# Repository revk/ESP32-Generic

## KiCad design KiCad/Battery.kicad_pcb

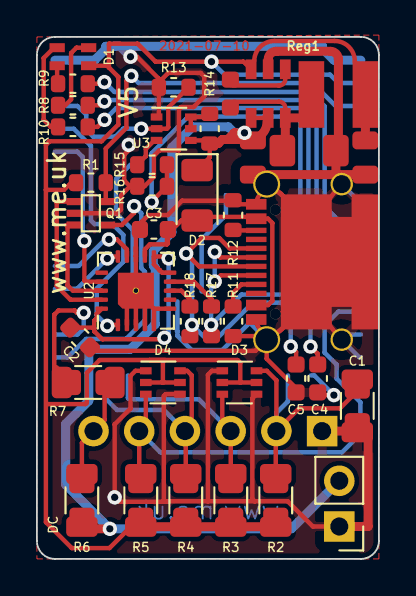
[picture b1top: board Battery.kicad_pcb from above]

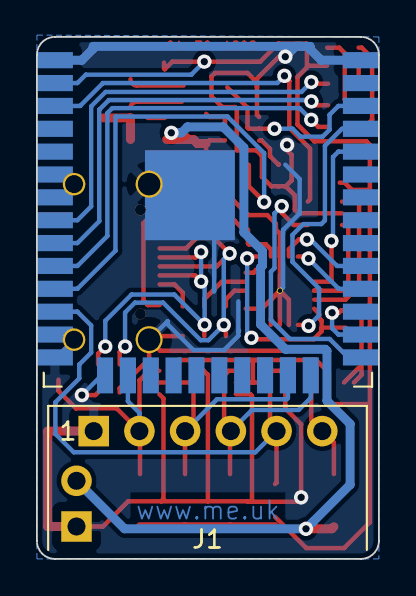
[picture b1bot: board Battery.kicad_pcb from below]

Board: 2 copper layers, 19.0 x 29.0 mm, 35 parts (2 on the bottom side), 35 nets.

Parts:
C1: NF; Pad_1206_0805_NF
C2: 100nF; C_0603
C3: 10nF; C_0603
C4, C5: 47pF; C_0603
D1: RGB; LED-RGB-1.6x1.6
D2: D; D_1206_3216Metric
D3, D4: BAV99S; SOT-363_SC-70-6
J1: Connector; Molex_MiniSPOX_H6RA_0.1
J2: USB-C; USC16-TR-Round
J3: DC; PinHeader_1x02_P2.54mm_Vertical
Q1: RN1701; USV-5
R1, R13, R14: 10K; R_0603
R2, R3, R4, R5, R6: NF; Pad_1206_0805_NF
R7: 0R; Pad_1206_0805_NF
R8: 324R; R_0603
R9: 732R; R_0603
R10: 1K; R_0603
R11, R12: 5K1; R_0603
R15: 18K; R_0603
R16: 1k; R_0603
R17, R18: 27R; R_0603
Reg1: Regulator; RegulatorBlock
U1: ESP32-WROOM-32
U2: FT231XQ; QFN-20-1EP_4x4mm_P0.5mm_EP2.5x2.5mm
U3: NX6020CAKS; SOT-363_SC-70-6

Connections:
+3V3: D1.1, D3.2, D3.5, D4.2, D4.5, R1.2, R2.1, R3.1, R4.1, R5.1, Reg1.4, U1.2
ADC: R15.2, R16.1, U1.11
ADCON: R13.2, U1.36, U3.2
B: R8.2, U1.9
CHARGER: U1.29, U2.14
D+: R18.1, U2.8
D-: R17.2, U2.9
DC: D2.1, J3.2, R6.1, R14.2, Reg1.1, Reg1.2, U3.4
EN: Q1.1, U2.19
G: R10.2, U1.10
GND: C1.1, C2.2, C3.1, C4.2, C5.2, D3.1, D3.4, D4.1, D4.4, J1.1, J2.A1, J2.A12, J2.B1, J2.B12, J2.S1, J3.1, Q1.2, R11.2, R12.1, R13.1, R16.2, Reg1.3, U1.1, U1.6, U1.7, U1.13, U1.14, U1.15, U1.38, U1.39, U2.2, U2.3, U2.4, U2.5, U2.6, U2.13, U2.21, U3.1
GPIO0: Q1.3, U2.18
I: U1.34, U2.17
IO1: C1.2, D3.6, J1.2, R2.2, U1.16
IO2: D3.3, J1.3, R3.2, U1.23
IO3: D4.6, J1.4, R4.2, U1.24
IO4: D4.3, J1.5, R5.2, U1.12
IO5: R7.1, U1.26
unnamed: C2.1, U2.10, U2.11, U2.20
unnamed: C4.1, J2.A7, J2.B7, R17.1
unnamed: C5.1, J2.A6, J2.B6, R18.2
unnamed: D1.2, R9.1
unnamed: D1.3, R10.1
unnamed: D1.4, R8.1
unnamed: J1.6, R6.2, R7.2
unnamed: J2.A5, R11.1
unnamed: J2.B5, R12.2
unnamed: Q1.4, U1.25
unnamed: Q1.5, R1.1, U1.3
unnamed: R14.1, U3.5, U3.6
unnamed: R15.1, U3.3
O: U1.35, U2.1
R: R9.2, U1.8
USB: U1.28, U2.15
VBUS: C3.2, D2.2, J2.A4, J2.A9, J2.B4, J2.B9, U2.12

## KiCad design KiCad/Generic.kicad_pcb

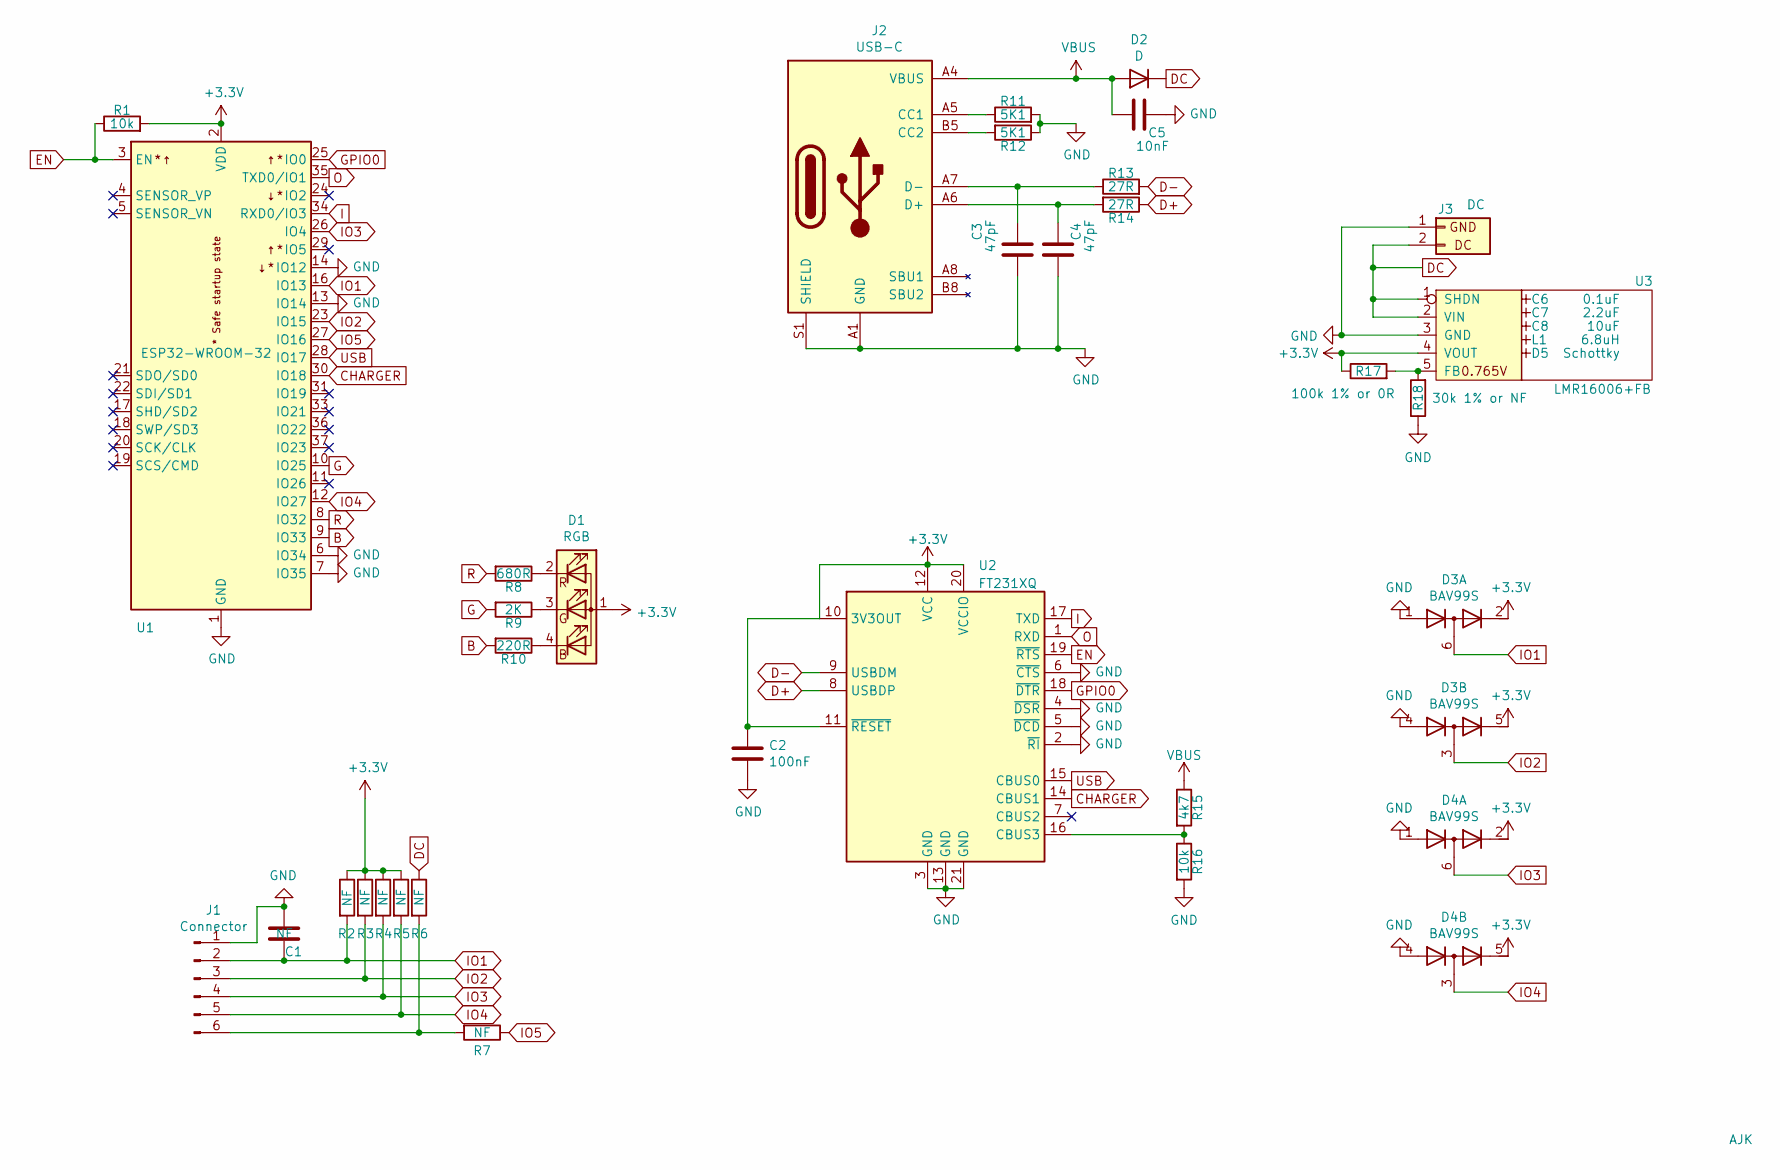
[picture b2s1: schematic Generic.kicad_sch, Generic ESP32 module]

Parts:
C1: NF; Pad_1206_0805_Open
C2: 100nF; C_0603
C3, C4: 47pF; C_0603
C5: 10nF; C_0603
C6: 0.1uF; Hidden
C7: 2.2uF; Hidden
C8: 10uF; Hidden
D1: RGB; LED-RGB-1.6x1.6; Part No APTF1616LSEEZGKQBKC
D2: D; D_1206_3216Metric
D3, D4: BAV99S; SOT-363_SC-70-6; Part No BAV99S
D5: Schottky; Hidden; Part No CD1206-B2100
J1: Connector; Molex_MiniSPOX_H6RA; Part No 0022057065
J2: USB-C; USC16-TR-Round; Part No CSP-USC16-TR
J3: DC
L1: 6.8uH; Hidden; Part No TYA4020
Logo1: AJK
R1, R16: 10k; R_0603
R2, R3, R4, R5, R6, R7: NF; Pad_1206_0805_Open
R8: 680R; R_0603
R9: 2K; R_0603
R10: 220R; R_0603
R11, R12: 5K1; R_0603
R13, R14: 27R; R_0603
R15: 4k7; R_0603
R17: 100k 1% or 0R; R_0603
R18: 30k 1% or NF; R_0603
U1: ESP32-WROOM-32
U2: FT231XQ; QFN-20-1EP_4x4mm_P0.5mm_EP2.5x2.5mm
U3: LMR16006+FB; RegulatorBlockFB; Part No LMR16006YQ3

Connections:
+3V3: C2.1, D1.1 (A), D3.2 (K2), D3.5 (K4), D4.2 (K2), D4.5 (K4), R1.2, R2.1, R3.1, R4.1, R5.1, R17.1, U1.2 (VDD), U2.10 (3V3OUT), U2.11 (~RESET), U2.12 (VCC), U2.20 (VCCIO), U3.4 (VOUT)
B: R10.2, U1.9 (IO33)
CHARGER: U1.30 (IO18), U2.14 (CBUS1)
D+: R14.1, U2.8 (USBDP)
D-: R13.2, U2.9 (USBDM)
DC: D2.1 (K), J3.2 (DC), R6.1, U3.1 (SHDN), U3.2 (VIN)
EN: R1.1, U1.3 (EN), U2.19 (~RTS)
G: R9.2, U1.10 (IO25)
GND: C1.1, C2.2, C3.2, C4.2, C5.1, D3.1 (A1), D3.4 (A3), D4.1 (A1), D4.4 (A3), J1.1, J2.A1 (GND), J2.A12 (GND), J2.B1 (GND), J2.B12 (GND), J2.S1 (SHIELD), J3.1 (GND), R11.2, R12.1, R16.2, R18.1, U1.1 (GND), U1.6 (IO34), U1.7 (IO35), U1.13 (IO14), U1.14 (IO12), U1.15 (GND), U1.38 (GND), U1.39 (GND), U2.2 (~RI), U2.3 (GND), U2.4 (~DSR), U2.5 (~DCD), U2.6 (~CTS), U2.13 (GND), U2.21 (GND), U3.3 (GND)
GPIO0: U1.25 (IO0), U2.18 (~DTR)
I: U1.34 (RXD0/IO3), U2.17 (TXD)
IO1: C1.2, D3.6 (K3A4), J1.2, R2.2, U1.16 (IO13)
IO2: D3.3 (K1A2), J1.3, R3.2, U1.23 (IO15)
IO3: D4.6 (K3A4), J1.4, R4.2, U1.26 (IO4)
IO4: D4.3 (K1A2), J1.5, R5.2, U1.12 (IO27)
IO5: R7.1, U1.27 (IO16)
unnamed: C3.1, J2.A7 (D-), J2.B7 (D-), R13.1
unnamed: C4.1, J2.A6 (D+), J2.B6 (D+), R14.2
unnamed: D1.2 (RK), R8.1
unnamed: D1.3 (GK), R9.1
unnamed: D1.4 (BK), R10.1
unnamed: J1.6, R6.2, R7.2
unnamed: J2.A5 (CC1), R11.1
unnamed: J2.B5 (CC2), R12.2
unnamed: R15.2, R16.1, U2.16 (CBUS3)
unnamed: R17.2, R18.2, U3.5 (FB)
O: U1.35 (TXD0/IO1), U2.1 (RXD)
R: R8.2, U1.8 (IO32)
USB: U1.28 (IO17), U2.15 (CBUS0)
VBUS: C5.2, D2.2 (A), J2.A4 (VBUS), J2.A9 (VBUS), J2.B4 (VBUS), J2.B9 (VBUS), R15.1

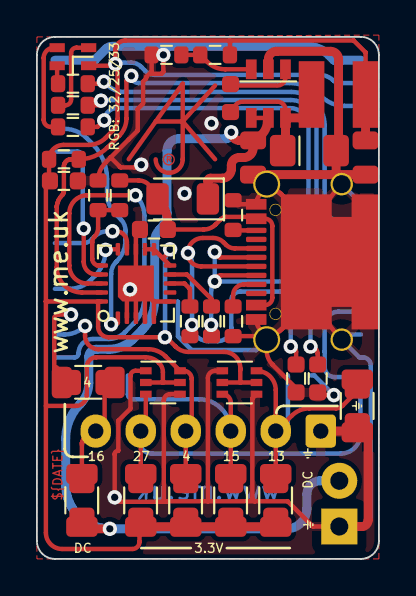
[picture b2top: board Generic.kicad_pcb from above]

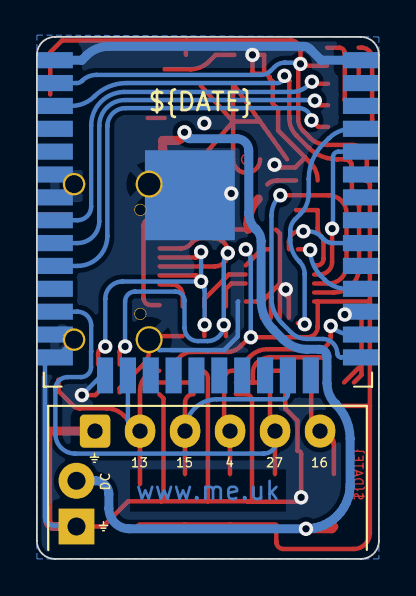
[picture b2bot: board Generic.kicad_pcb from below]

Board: 2 copper layers, 19.0 x 29.0 mm, 39 parts (2 on the bottom side), 30 nets.

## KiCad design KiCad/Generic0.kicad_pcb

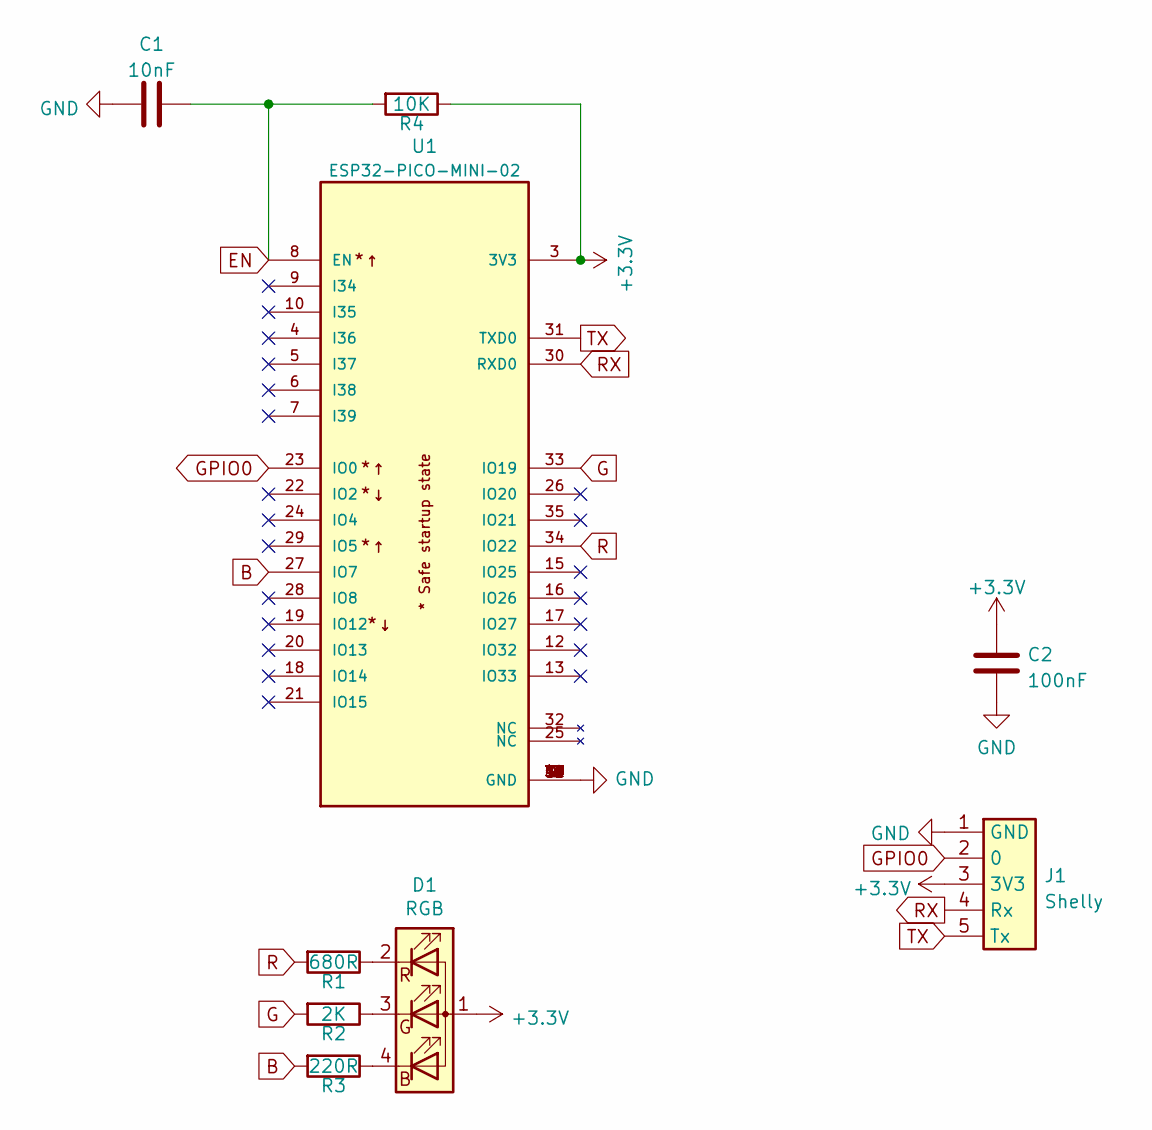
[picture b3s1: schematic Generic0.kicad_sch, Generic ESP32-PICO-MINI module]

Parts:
C1: 10nF; C_0603
C2: 100nF; C_0603
D1: RGB; LED-RGB-1.6x1.6; Part No APTF1616LSEEZGKQBKC
J1: Shelly
R1: 680R; R_0603
R2: 2K; R_0603
R3: 220R; R_0603
R4: 10K; Pad_0603_Bridged
U1: ESP32-PICO-MINI-02; PARTREV v1.0

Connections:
+3V3: C2.1, D1.1 (A), J1.3 (3V3), R4.1, U1.3 (3V3)
B: R3.2, U1.27 (IO7)
EN: C1.2, R4.2, U1.8 (EN)
G: R2.2, U1.33 (IO19)
GND: C1.1, C2.2, J1.1 (GND), U1.1 (GND), U1.2 (GND), U1.11 (GND), U1.14 (GND), U1.36 (GND), U1.37 (GND), U1.38 (GND), U1.39 (GND), U1.40 (GND), U1.41 (GND), U1.42 (GND), U1.43 (GND), U1.44 (GND), U1.45 (GND), U1.46 (GND), U1.47 (GND), U1.48 (GND), U1.49 (GND), U1.50 (GND), U1.51 (GND), U1.52 (GND), U1.53 (GND)
GPIO0: J1.2 (0), U1.23 (IO0)
unnamed: D1.2 (RK), R1.1
unnamed: D1.3 (GK), R2.1
unnamed: D1.4 (BK), R3.1
R: R1.2, U1.34 (IO22)
RX: J1.4 (Rx), U1.30 (RXD0)
TX: J1.5 (Tx), U1.31 (TXD0)

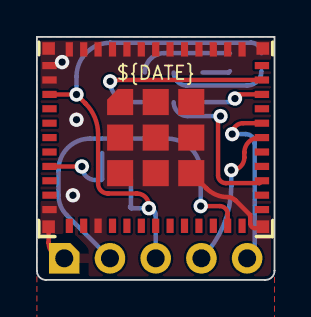
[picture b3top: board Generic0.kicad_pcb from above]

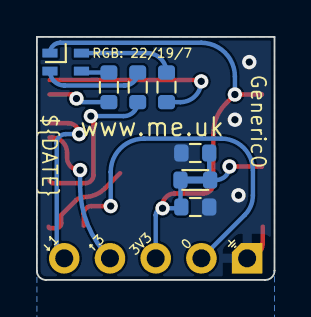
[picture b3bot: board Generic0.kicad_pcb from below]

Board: 2 copper layers, 13.2 x 13.5 mm, 9 parts (8 on the bottom side), 12 nets.

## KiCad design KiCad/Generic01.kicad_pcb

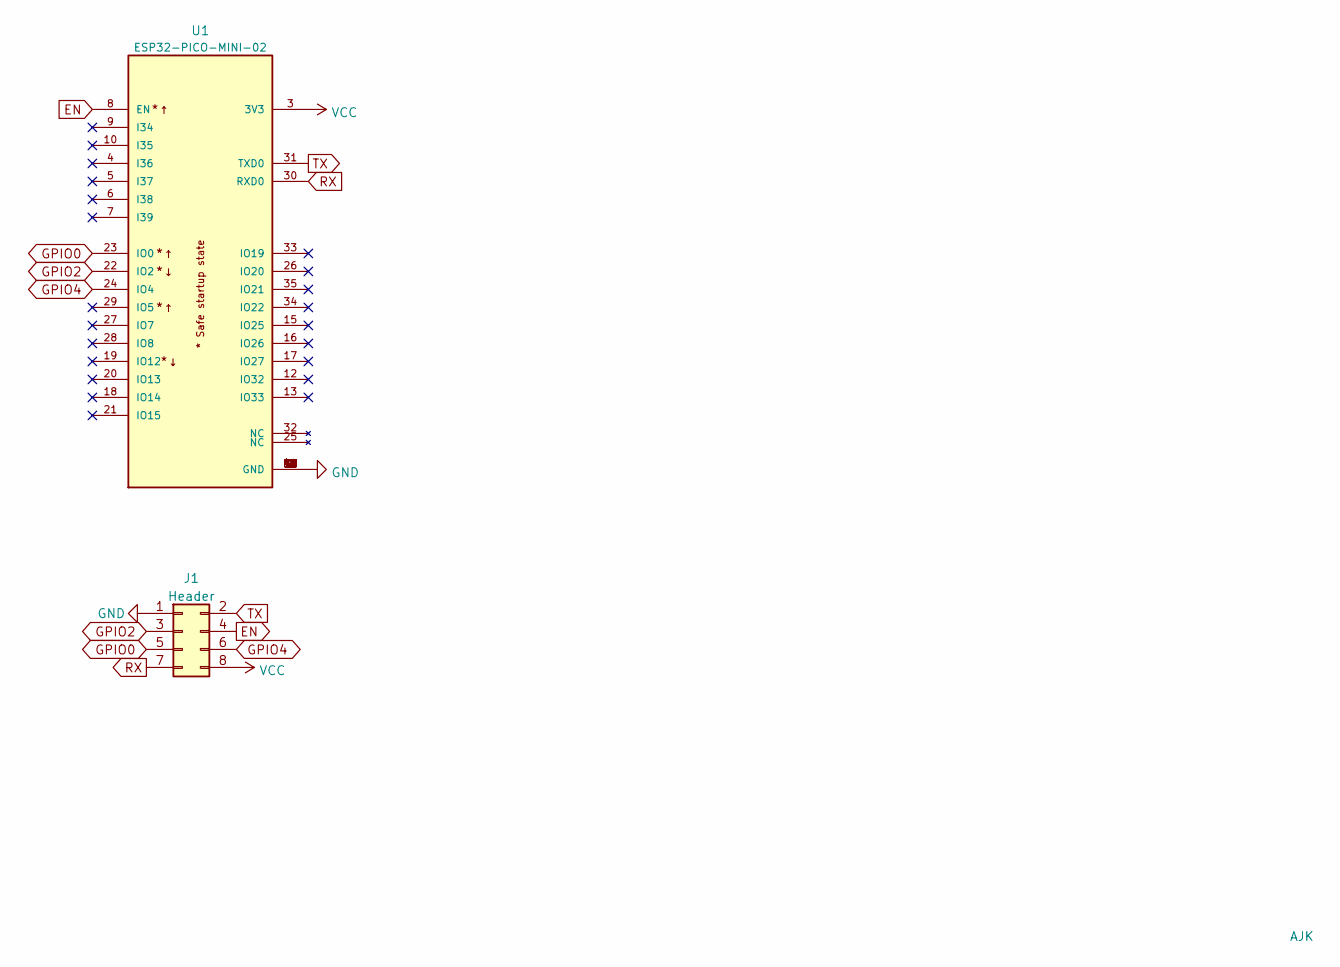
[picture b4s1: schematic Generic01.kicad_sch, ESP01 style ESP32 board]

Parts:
J1: Header; PinHeader_2x04_P2.54mm_Vertical
Logo1: AJK
U1: ESP32-PICO-MINI-02; PARTREV v1.0

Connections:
EN: J1.4, U1.8 (EN)
GND: J1.1, U1.1 (GND), U1.2 (GND), U1.11 (GND), U1.14 (GND), U1.36 (GND), U1.37 (GND), U1.38 (GND), U1.39 (GND), U1.40 (GND), U1.41 (GND), U1.42 (GND), U1.43 (GND), U1.44 (GND), U1.45 (GND), U1.46 (GND), U1.47 (GND), U1.48 (GND), U1.49 (GND), U1.50 (GND), U1.51 (GND), U1.52 (GND), U1.53 (GND)
GPIO0: J1.5, U1.23 (IO0)
GPIO2: J1.3, U1.22 (IO2)
GPIO4: J1.6, U1.24 (IO4)
RX: J1.7, U1.30 (RXD0)
TX: J1.2, U1.31 (TXD0)
VCC: J1.8, U1.3 (3V3)

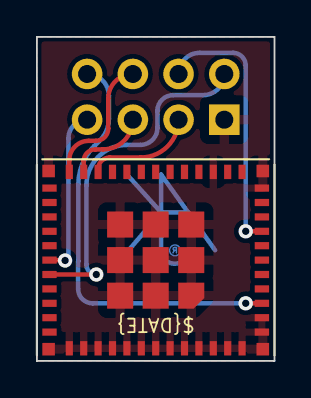
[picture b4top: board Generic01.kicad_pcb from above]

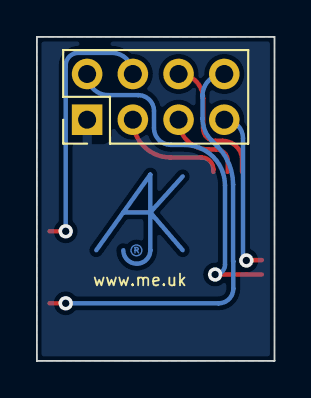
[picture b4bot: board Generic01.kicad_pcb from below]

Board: 2 copper layers, 13.2 x 18.0 mm, 3 parts (2 on the bottom side), 8 nets.

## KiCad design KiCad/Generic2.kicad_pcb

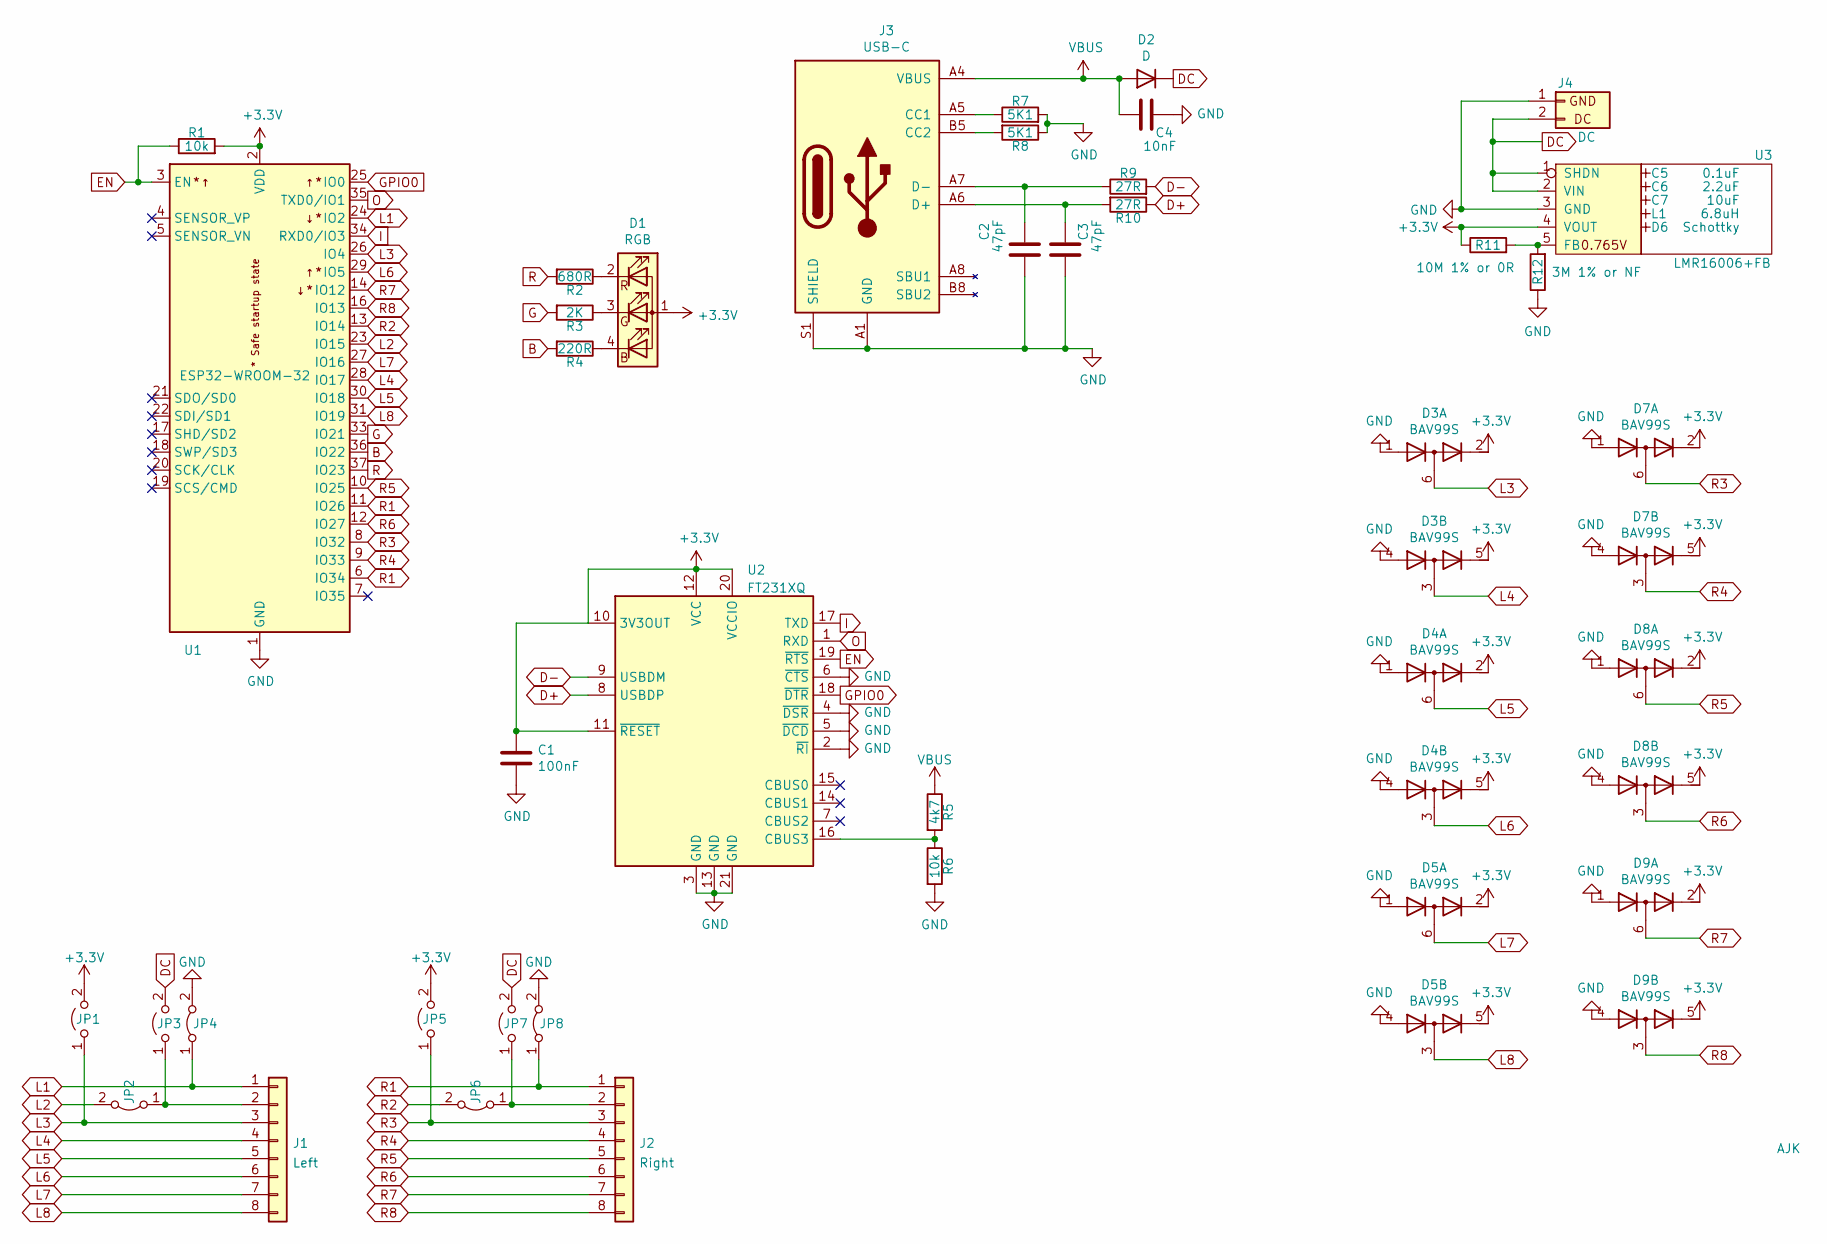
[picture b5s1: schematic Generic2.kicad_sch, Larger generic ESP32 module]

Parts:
C1: 100nF; C_0603
C2, C3: 47pF; C_0603
C4: 10nF; C_0603
C5: 0.1uF; Hidden
C6: 2.2uF; Hidden
C7: 10uF; Hidden
D1: RGB; LED-RGB-1.6x1.6; Part No APTF1616LSEEZGKQBKC
D2: D; D_1206_3216Metric
D3, D4, D5, D7, D8, D9: BAV99S; SOT-363_SC-70-6; Part No BAV99S
D6: Schottky; Hidden; Part No CD1206-B2100
J1: Left; Molex_MiniSPOX_H8RA
J2: Right; Molex_MiniSPOX_H8RA
J3: USB-C; USC16-TR-Round; Part No CSP-USC16-TR
J4: DC; PinHeader_1x02_P2.54mm_Vertical
JP1, JP5: L3; Pad_1206_0805_Open
JP2, JP6: L2; Pad_1206_0805_Bridged
JP3, JP7: L2; Pad_1206_0805_Open
JP4, JP8: L1; Pad_1206_0805_Bridged
L1: 6.8uH; Hidden; Part No TYA4020
Logo1: AJK
R1, R6: 10k; R_0603
R2: 680R; R_0603
R3: 2K; R_0603
R4: 220R; R_0603
R5: 4k7; R_0603
R7, R8: 5K1; R_0603
R9, R10: 27R; R_0603
R11: 10M 1% or 0R; R_0603
R12: 3M 1% or NF; R_0603
U1: ESP32-WROOM-32
U2: FT231XQ; QFN-20-1EP_4x4mm_P0.5mm_EP2.5x2.5mm
U3: LMR16006+FB; RegulatorBlockFB; Part No LMR16006YQ3

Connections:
+3V3: C1.1, D1.1 (A), D3.2 (K2), D3.5 (K4), D4.2 (K2), D4.5 (K4), D5.2 (K2), D5.5 (K4), D7.2 (K2), D7.5 (K4), D8.2 (K2), D8.5 (K4), D9.2 (K2), D9.5 (K4), JP1.2 (B), JP5.2 (B), R1.2, R11.1, U1.2 (VDD), U2.10 (3V3OUT), U2.11 (~RESET), U2.12 (VCC), U2.20 (VCCIO), U3.4 (VOUT)
B: R4.2, U1.36 (IO22)
D+: R10.1, U2.8 (USBDP)
D-: R9.2, U2.9 (USBDM)
DC: D2.1 (K), J4.2 (DC), JP3.2 (B), JP7.2 (B), U3.1 (SHDN), U3.2 (VIN)
EN: R1.1, U1.3 (EN), U2.19 (~RTS)
G: R3.2, U1.33 (IO21)
GND: C1.2, C2.2, C3.2, C4.1, D3.1 (A1), D3.4 (A3), D4.1 (A1), D4.4 (A3), D5.1 (A1), D5.4 (A3), D7.1 (A1), D7.4 (A3), D8.1 (A1), D8.4 (A3), D9.1 (A1), D9.4 (A3), J3.A1 (GND), J3.A12 (GND), J3.B1 (GND), J3.B12 (GND), J3.S1 (SHIELD), J4.1 (GND), JP4.2 (B), JP8.2 (B), R6.2, R7.2, R8.1, R12.1, U1.1 (GND), U1.15 (GND), U1.38 (GND), U1.39 (GND), U2.2 (~RI), U2.3 (GND), U2.4 (~DSR), U2.5 (~DCD), U2.6 (~CTS), U2.13 (GND), U2.21 (GND), U3.3 (GND)
GPIO0: U1.25 (IO0), U2.18 (~DTR)
I: U1.34 (RXD0/IO3), U2.17 (TXD)
L1: J1.1, JP4.1 (A), U1.24 (IO2)
L2: JP2.2 (B), U1.23 (IO15)
L3: D3.6 (K3A4), J1.3, JP1.1 (A), U1.26 (IO4)
L4: D3.3 (K1A2), J1.4, U1.28 (IO17)
L5: D4.6 (K3A4), J1.5, U1.30 (IO18)
L6: D4.3 (K1A2), J1.6, U1.29 (IO5)
L7: D5.6 (K3A4), J1.7, U1.27 (IO16)
L8: D5.3 (K1A2), J1.8, U1.31 (IO19)
unnamed: C2.1, J3.A7 (D-), J3.B7 (D-), R9.1
unnamed: C3.1, J3.A6 (D+), J3.B6 (D+), R10.2
unnamed: D1.2 (RK), R2.1
unnamed: D1.3 (GK), R3.1
unnamed: D1.4 (BK), R4.1
unnamed: J1.2, JP2.1 (A), JP3.1 (A)
unnamed: J2.2, JP6.1 (A), JP7.1 (A)
unnamed: J3.A5 (CC1), R7.1
unnamed: J3.B5 (CC2), R8.2
unnamed: R5.2, R6.1, U2.16 (CBUS3)
unnamed: R11.2, R12.2, U3.5 (FB)
O: U1.35 (TXD0/IO1), U2.1 (RXD)
R: R2.2, U1.37 (IO23)
R1: J2.1, JP8.1 (A), U1.6 (IO34), U1.11 (IO26)
R2: JP6.2 (B), U1.13 (IO14)
R3: D7.6 (K3A4), J2.3, JP5.1 (A), U1.8 (IO32)
R4: D7.3 (K1A2), J2.4, U1.9 (IO33)
R5: D8.6 (K3A4), J2.5, U1.10 (IO25)
R6: D8.3 (K1A2), J2.6, U1.12 (IO27)
R7: D9.6 (K3A4), J2.7, U1.14 (IO12)
R8: D9.3 (K1A2), J2.8, U1.16 (IO13)
VBUS: C4.2, D2.2 (A), J3.A4 (VBUS), J3.A9 (VBUS), J3.B4 (VBUS), J3.B9 (VBUS), R5.1

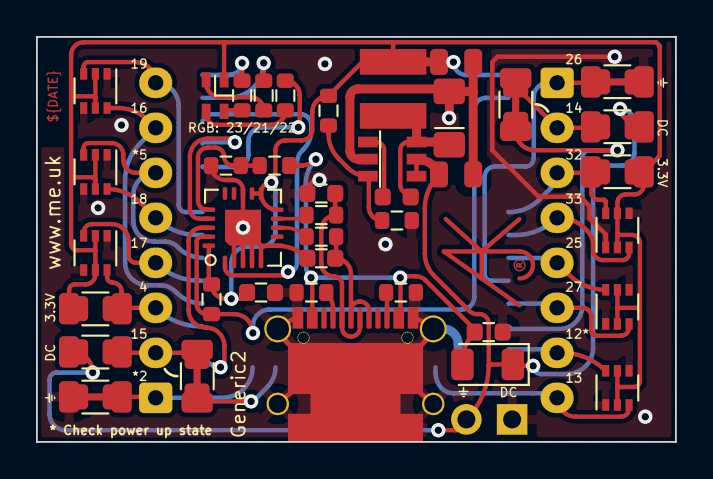
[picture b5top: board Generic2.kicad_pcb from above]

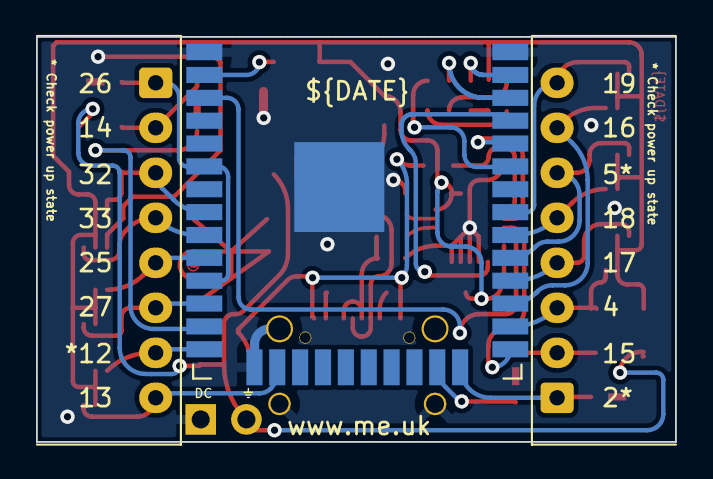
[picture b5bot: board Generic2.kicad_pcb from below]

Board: 2 copper layers, 35.5 x 22.5 mm, 45 parts (4 on the bottom side), 40 nets.

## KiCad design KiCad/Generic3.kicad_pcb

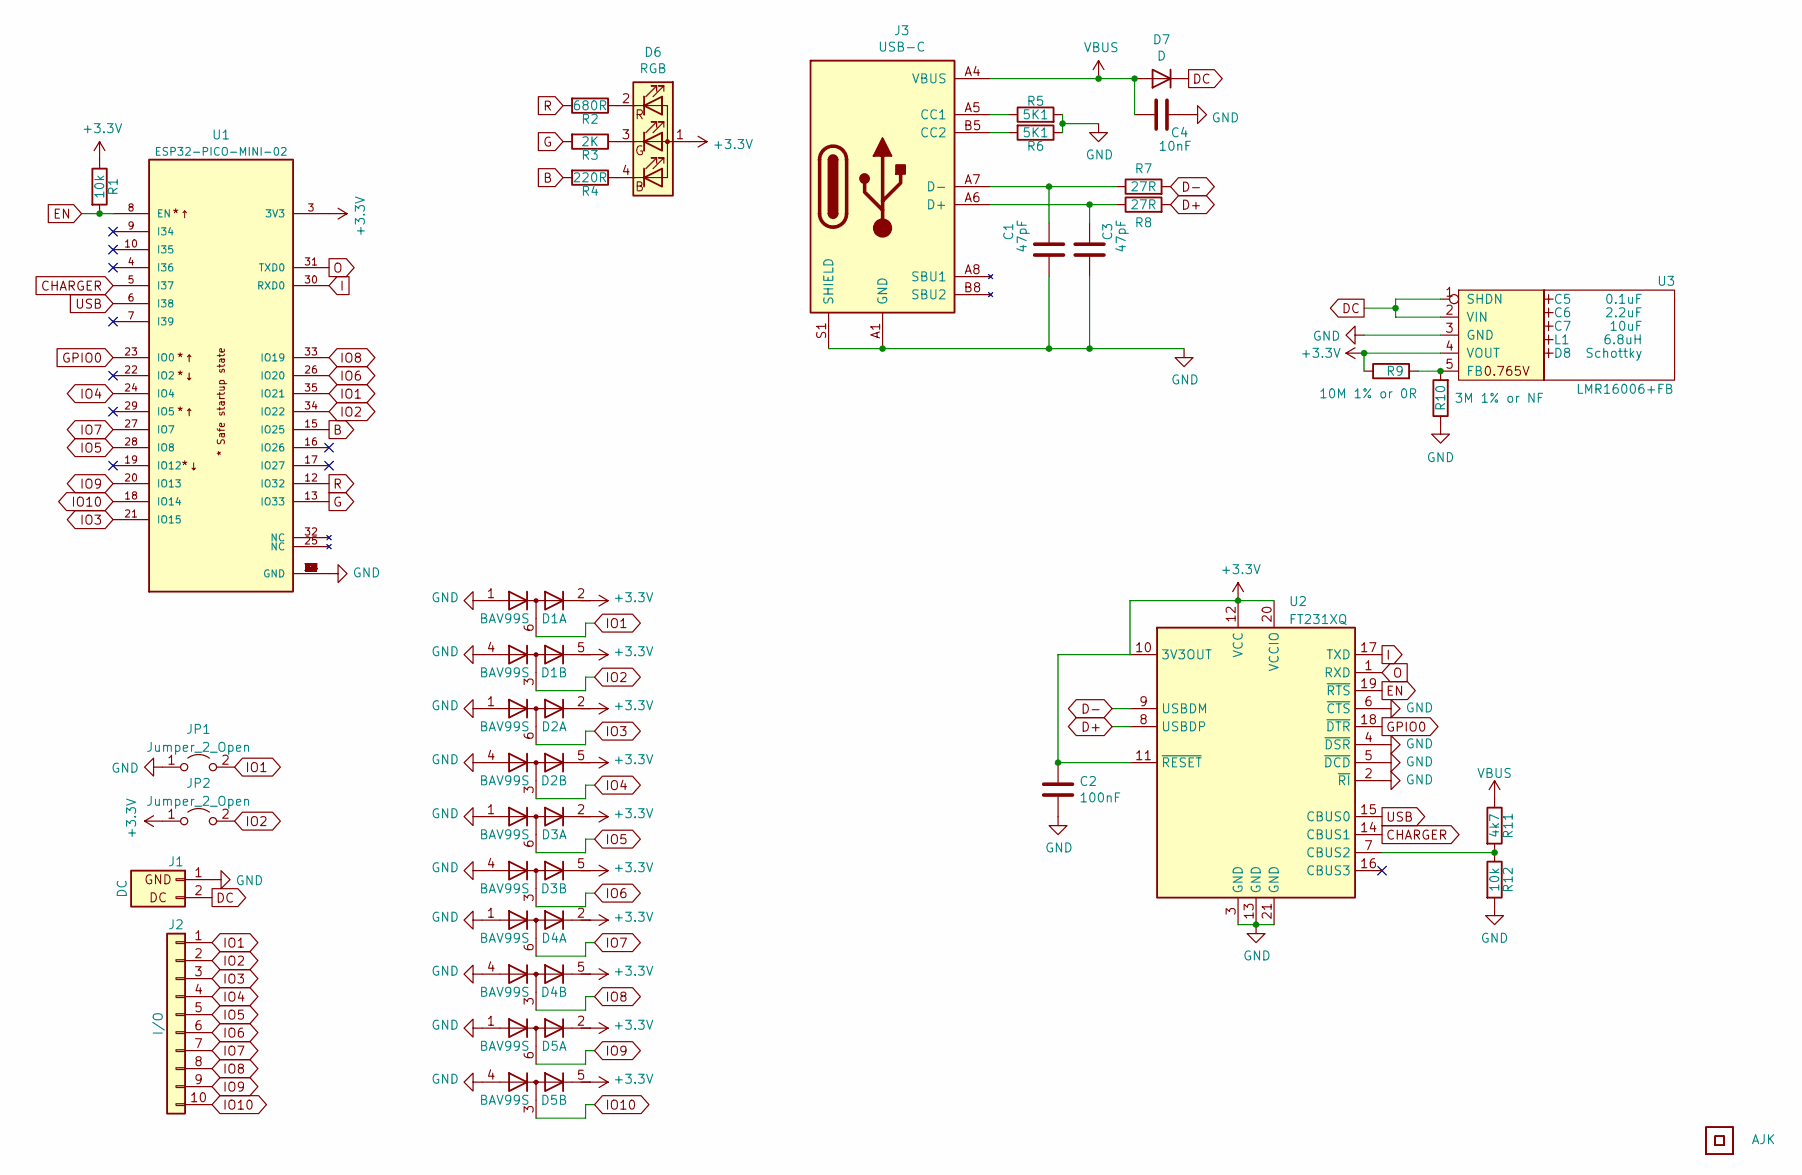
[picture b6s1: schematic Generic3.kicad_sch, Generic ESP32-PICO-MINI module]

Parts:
C1, C3: 47pF; C_0603
C2: 100nF; C_0603
C4: 10nF; C_0603
C5: 0.1uF; Hidden
C6: 2.2uF; Hidden
C7: 10uF; Hidden
D1, D2, D3, D4, D5: BAV99S; SOT-363_SC-70-6
D6: RGB; LED-RGB-1.6x1.6; Part No APTF1616LSEEZGKQBKC
D7: D; D_1206
D8: Schottky; Hidden; Part No CD1206-B2100
J1: DC; Molex_MiniSPOX_H2RA
J2: I/O; Molex_MiniSPOX_H10RA
J3: USB-C; USC16-TR-Round; Part No CSP-USC16-TR
JP1, JP2: Jumper_2_Open; Pad_1206_0805_Open
L1: 6.8uH; Hidden; Part No TYA4020
Logo1: AJK
R1, R12: 10k; R_0603
R2: 680R; R_0603
R3: 2K; R_0603
R4: 220R; R_0603
R5, R6: 5K1; R_0603
R7, R8: 27R; R_0603
R9: 10M 1% or 0R; R_0603
R10: 3M 1% or NF; R_0603
R11: 4k7; R_0603
U1: ESP32-PICO-MINI-02; PARTREV v1.0
U2: FT231XQ; QFN-20-1EP_4x4mm_P0.5mm_EP2.5x2.5mm
U3: LMR16006+FB; RegulatorBlockFB; Part No LMR16006YQ3
U4: QR; QR-GENERIC

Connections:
+3V3: C2.1, D1.2 (K2), D1.5 (K4), D2.2 (K2), D2.5 (K4), D3.2 (K2), D3.5 (K4), D4.2 (K2), D4.5 (K4), D5.2 (K2), D5.5 (K4), D6.1 (A), JP2.1 (A), R1.1, R9.1, U1.3 (3V3), U2.10 (3V3OUT), U2.11 (~RESET), U2.12 (VCC), U2.20 (VCCIO), U3.4 (VOUT)
B: R4.2, U1.15 (IO25)
CHARGER: U1.5 (I37), U2.14 (CBUS1)
D+: R8.2, U2.8 (USBDP)
D-: R7.2, U2.9 (USBDM)
DC: D7.1 (K), J1.2 (DC), U3.1 (SHDN), U3.2 (VIN)
EN: R1.2, U1.8 (EN), U2.19 (~RTS)
G: R3.2, U1.13 (IO33)
GND: C1.2, C2.2, C3.2, C4.1, D1.1 (A1), D1.4 (A3), D2.1 (A1), D2.4 (A3), D3.1 (A1), D3.4 (A3), D4.1 (A1), D4.4 (A3), D5.1 (A1), D5.4 (A3), J1.1 (GND), J3.A1 (GND), J3.A12 (GND), J3.B1 (GND), J3.B12 (GND), J3.S1 (SHIELD), JP1.1 (A), R5.2, R6.1, R10.1, R12.2, U1.1 (GND), U1.2 (GND), U1.11 (GND), U1.14 (GND), U1.36 (GND), U1.37 (GND), U1.38 (GND), U1.39 (GND), U1.40 (GND), U1.41 (GND), U1.42 (GND), U1.43 (GND), U1.44 (GND), U1.45 (GND), U1.46 (GND), U1.47 (GND), U1.48 (GND), U1.49 (GND), U1.50 (GND), U1.51 (GND), U1.52 (GND), U1.53 (GND), U2.2 (~RI), U2.3 (GND), U2.4 (~DSR), U2.5 (~DCD), U2.6 (~CTS), U2.13 (GND), U2.21 (GND), U3.3 (GND)
GPIO0: U1.23 (IO0), U2.18 (~DTR)
I: U1.30 (RXD0), U2.17 (TXD)
IO1: D1.6 (K3A4), J2.1, JP1.2 (B), U1.35 (IO21)
IO2: D1.3 (K1A2), J2.2, JP2.2 (B), U1.34 (IO22)
IO3: D2.6 (K3A4), J2.3, U1.21 (IO15)
IO4: D2.3 (K1A2), J2.4, U1.24 (IO4)
IO5: D3.6 (K3A4), J2.5, U1.28 (IO8)
IO6: D3.3 (K1A2), J2.6, U1.26 (IO20)
IO7: D4.6 (K3A4), J2.7, U1.27 (IO7)
IO8: D4.3 (K1A2), J2.8, U1.33 (IO19)
IO9: D5.6 (K3A4), J2.9, U1.20 (IO13)
IO10: D5.3 (K1A2), J2.10, U1.18 (IO14)
unnamed: C1.1, J3.A7 (D-), J3.B7 (D-), R7.1
unnamed: C3.1, J3.A6 (D+), J3.B6 (D+), R8.1
unnamed: D6.2 (RK), R2.1
unnamed: D6.3 (GK), R3.1
unnamed: D6.4 (BK), R4.1
unnamed: J3.A5 (CC1), R5.1
unnamed: J3.B5 (CC2), R6.2
unnamed: R9.2, R10.2, U3.5 (FB)
unnamed: R11.2, R12.1, U2.7 (CBUS2)
O: U1.31 (TXD0), U2.1 (RXD)
R: R2.2, U1.12 (IO32)
USB: U1.6 (I38), U2.15 (CBUS0)
VBUS: C4.2, D7.2 (A), J3.A4 (VBUS), J3.A9 (VBUS), J3.B4 (VBUS), J3.B9 (VBUS), R11.1

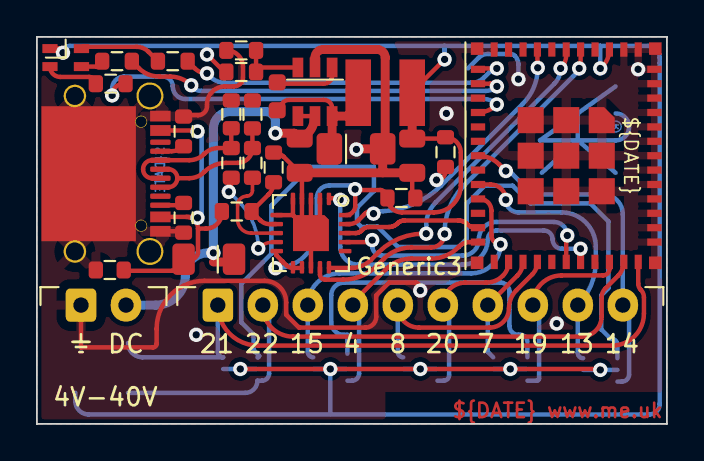
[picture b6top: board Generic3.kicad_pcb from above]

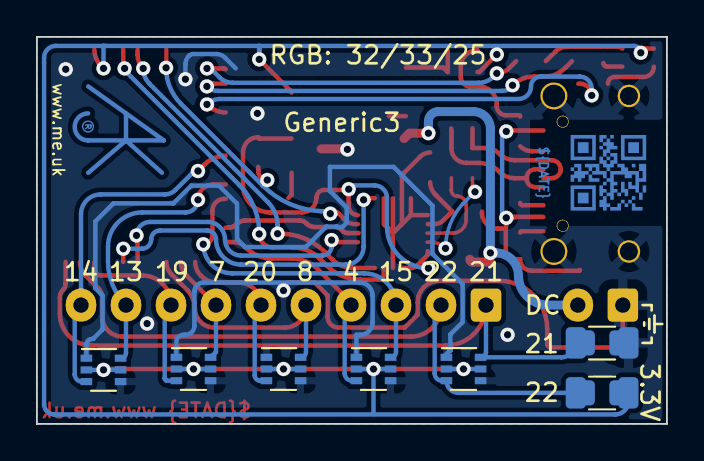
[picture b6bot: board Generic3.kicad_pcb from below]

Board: 2 copper layers, 35.0 x 21.5 mm, 38 parts (9 on the bottom side), 34 nets.

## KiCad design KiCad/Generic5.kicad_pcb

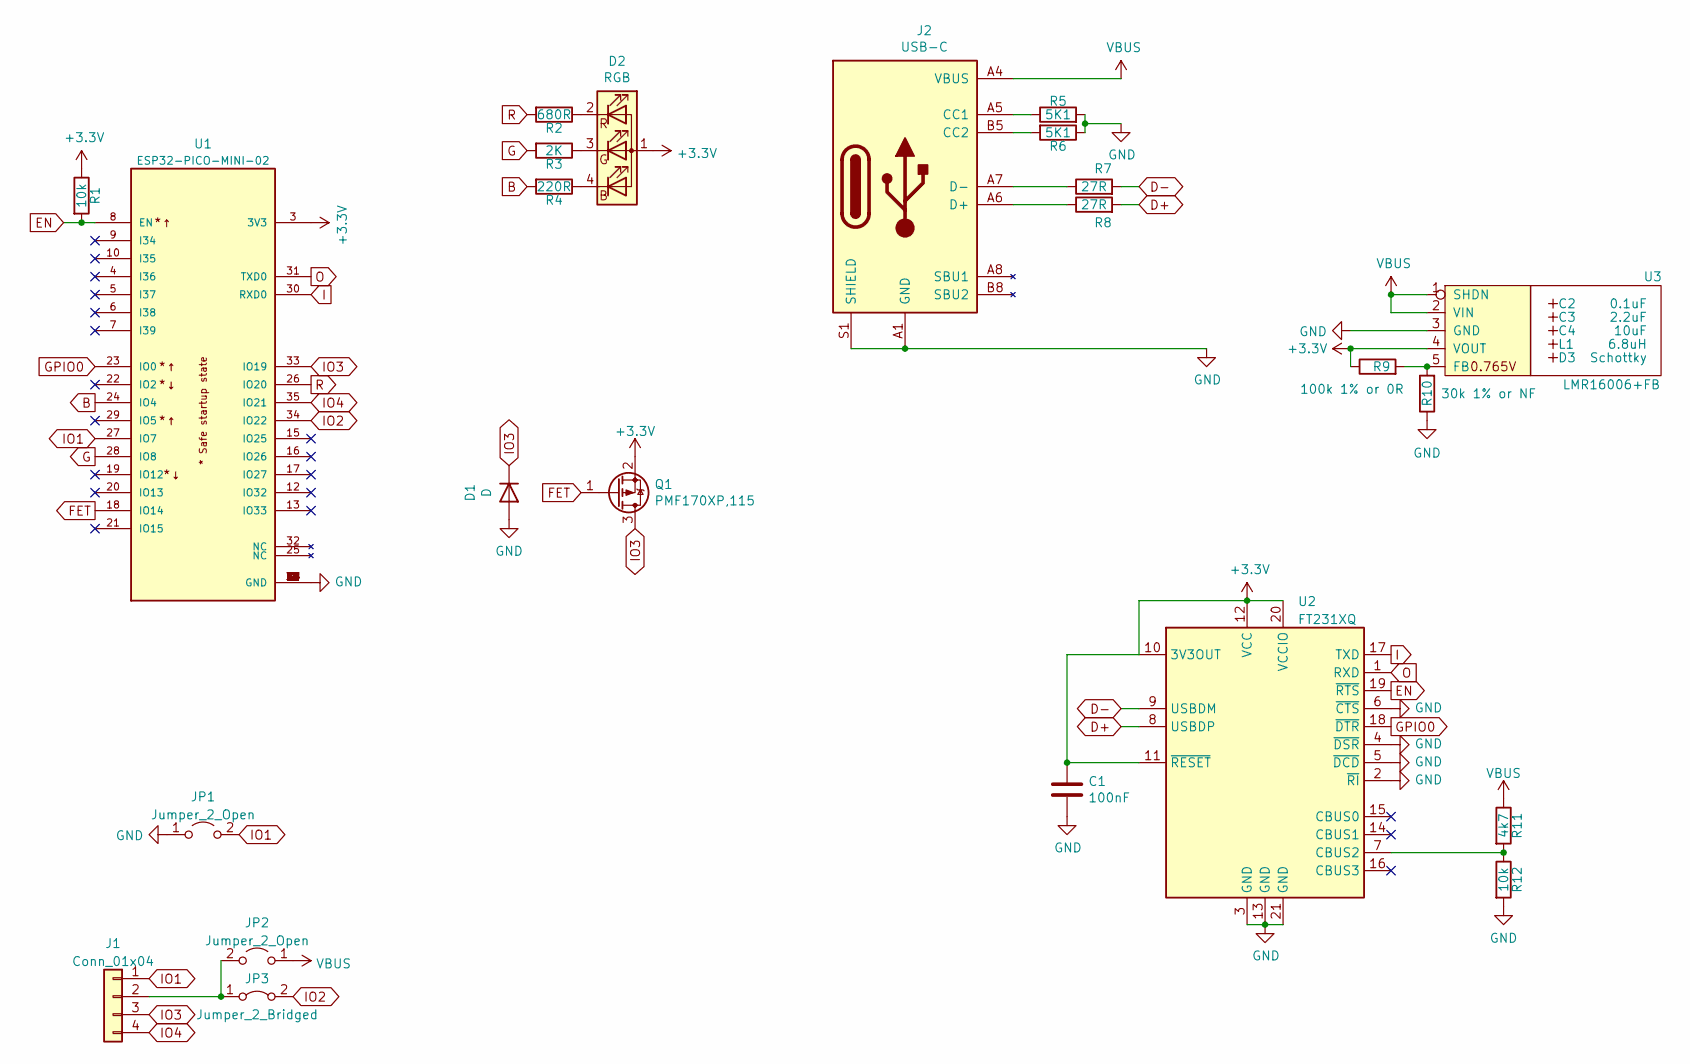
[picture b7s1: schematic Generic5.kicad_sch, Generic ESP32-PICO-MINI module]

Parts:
C1: 100nF; C_0603
C2: 0.1uF; Hidden
C3: 2.2uF; Hidden
C4: 10uF; Hidden
D1: D; D_1206
D2: RGB; LED-RGB-1.6x1.6; Part No APTF1616LSEEZGKQBKC
D3: Schottky; Hidden; Part No CD1206-B2100
J1: Conn_01x04; Molex_MiniSPOX_H4RA
J2: USB-C; USC16-TR-Round; Part No CSP-USC16-TR
JP1, JP2: Jumper_2_Open; Pad_0603_Open
JP3: Jumper_2_Bridged; Pad_0603_Bridged
L1: 6.8uH; Hidden; Part No TYA4020
Q1: PMF170XP,115; SOT-323_SC-70
R1, R12: 10k; R_0603
R2: 680R; R_0603
R3: 2K; R_0603
R4: 220R; R_0603
R5, R6: 5K1; R_0603
R7, R8: 27R; R_0603
R9: 100k 1% or 0R; R_0603
R10: 30k 1% or NF; R_0603
R11: 4k7; R_0603
U1: ESP32-PICO-MINI-02; PARTREV v1.0
U2: FT231XQ; QFN-20-1EP_4x4mm_P0.5mm_EP2.5x2.5mm
U3: LMR16006+FB; RegulatorBlockFB; Part No LMR16006YQ3

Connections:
+3V3: C1.1, D2.1 (A), Q1.2 (S), R1.1, R9.1, U1.3 (3V3), U2.10 (3V3OUT), U2.11 (~RESET), U2.12 (VCC), U2.20 (VCCIO), U3.4 (VOUT)
B: R4.2, U1.24 (IO4)
D+: R8.2, U2.8 (USBDP)
D-: R7.2, U2.9 (USBDM)
EN: R1.2, U1.8 (EN), U2.19 (~RTS)
FET: Q1.1 (G), U1.18 (IO14)
G: R3.2, U1.28 (IO8)
GND: C1.2, D1.2 (A), J2.A1 (GND), J2.A12 (GND), J2.B1 (GND), J2.B12 (GND), J2.S1 (SHIELD), JP1.1 (A), R5.2, R6.1, R10.1, R12.2, U1.1 (GND), U1.2 (GND), U1.11 (GND), U1.14 (GND), U1.36 (GND), U1.37 (GND), U1.38 (GND), U1.39 (GND), U1.40 (GND), U1.41 (GND), U1.42 (GND), U1.43 (GND), U1.44 (GND), U1.45 (GND), U1.46 (GND), U1.47 (GND), U1.48 (GND), U1.49 (GND), U1.50 (GND), U1.51 (GND), U1.52 (GND), U1.53 (GND), U2.2 (~RI), U2.3 (GND), U2.4 (~DSR), U2.5 (~DCD), U2.6 (~CTS), U2.13 (GND), U2.21 (GND), U3.3 (GND)
GPIO0: U1.23 (IO0), U2.18 (~DTR)
I: U1.30 (RXD0), U2.17 (TXD)
IO1: J1.1, JP1.2 (B), U1.27 (IO7)
IO2: JP3.2 (B), U1.34 (IO22)
IO3: D1.1 (K), J1.3, Q1.3 (D), U1.33 (IO19)
IO4: J1.4, U1.35 (IO21)
unnamed: D2.2 (RK), R2.1
unnamed: D2.3 (GK), R3.1
unnamed: D2.4 (BK), R4.1
unnamed: J1.2, JP2.2 (B), JP3.1 (A)
unnamed: J2.A5 (CC1), R5.1
unnamed: J2.A6 (D+), J2.B6 (D+), R8.1
unnamed: J2.A7 (D-), J2.B7 (D-), R7.1
unnamed: J2.B5 (CC2), R6.2
unnamed: R9.2, R10.2, U3.5 (FB)
unnamed: R11.2, R12.1, U2.7 (CBUS2)
O: U1.31 (TXD0), U2.1 (RXD)
R: R2.2, U1.26 (IO20)
VBUS: J2.A4 (VBUS), J2.A9 (VBUS), J2.B4 (VBUS), J2.B9 (VBUS), JP2.1 (A), R11.1, U3.1 (SHDN), U3.2 (VIN)
